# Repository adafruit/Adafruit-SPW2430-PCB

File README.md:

## Adafruit Silicon MEMS Microphone Breakout SPW2430 PCB
<a href="http://www.adafruit.com/products/2716"><br/>
Click here to purchase one from the Adafruit shop</a>

Listen to this good news - we now have a breakout board for a super tiny MEMS microphone. Just like 'classic' electret microphones, MEMS mics can detect sound and convert it to voltage, but they don't need a bias resistor or amplifier, its all in one! The SPW2430 is a small, low cost MEMS mic with a range of 100Hz - 10KHz, good for just about all general audio recording/detection.

This breakout is best used for projects such as voice changers, audio recording/sampling, and audio-reactive projects that use FFT. To keep the breakout small and simple, we only added a 3V voltage regulator (the microphone requires 3.3V DC) and filter capacitors. No additional opamp is included, the output peak-to-peak voltage has a 0.67V DC bias and about 100mVpp (peak-to-peak) when talking near the microphone, which is good for attaching to something that expects 'line level' input without clipping. The peak-to-peak can be as high as 1Vpp if there's a very loud sound. If you are If you need a microphone with adjustable gain or auto-gain control, check out our mic+amplifier options. If you need a higher peak-to-peak, a rail-to-rail op-amp and some resistors can get you boosted up!

Using it is simple: connect GND to ground, Vin to 3.3-5VDC. For the best performance, use the "quietest" supply available (on an Arduino, this would be the 3.3V supply). The audio waveform will come out of the DC pin. The output will have a DC bias of 0.67V so when its perfectly quiet that's what you'll read, there's a little drift. If the audio equipment you're using requires AC coupled audio, you can grab the signal out of the AC pin, which has a 10uF capacitor in series.

This repo contains the PCB files for the Adafruit SPW2430 Breakout

### License

Adafruit invests time and resources providing this open source design, please support Adafruit and open-source hardware by purchasing products from [Adafruit](https://www.adafruit.com)!

All text above must be included in any redistribution

Designed by Limor Fried/Ladyada for Adafruit Industries.
Creative Commons Attribution/Share-Alike, all text above must be included in any redistribution. 
See license.txt for additional information.

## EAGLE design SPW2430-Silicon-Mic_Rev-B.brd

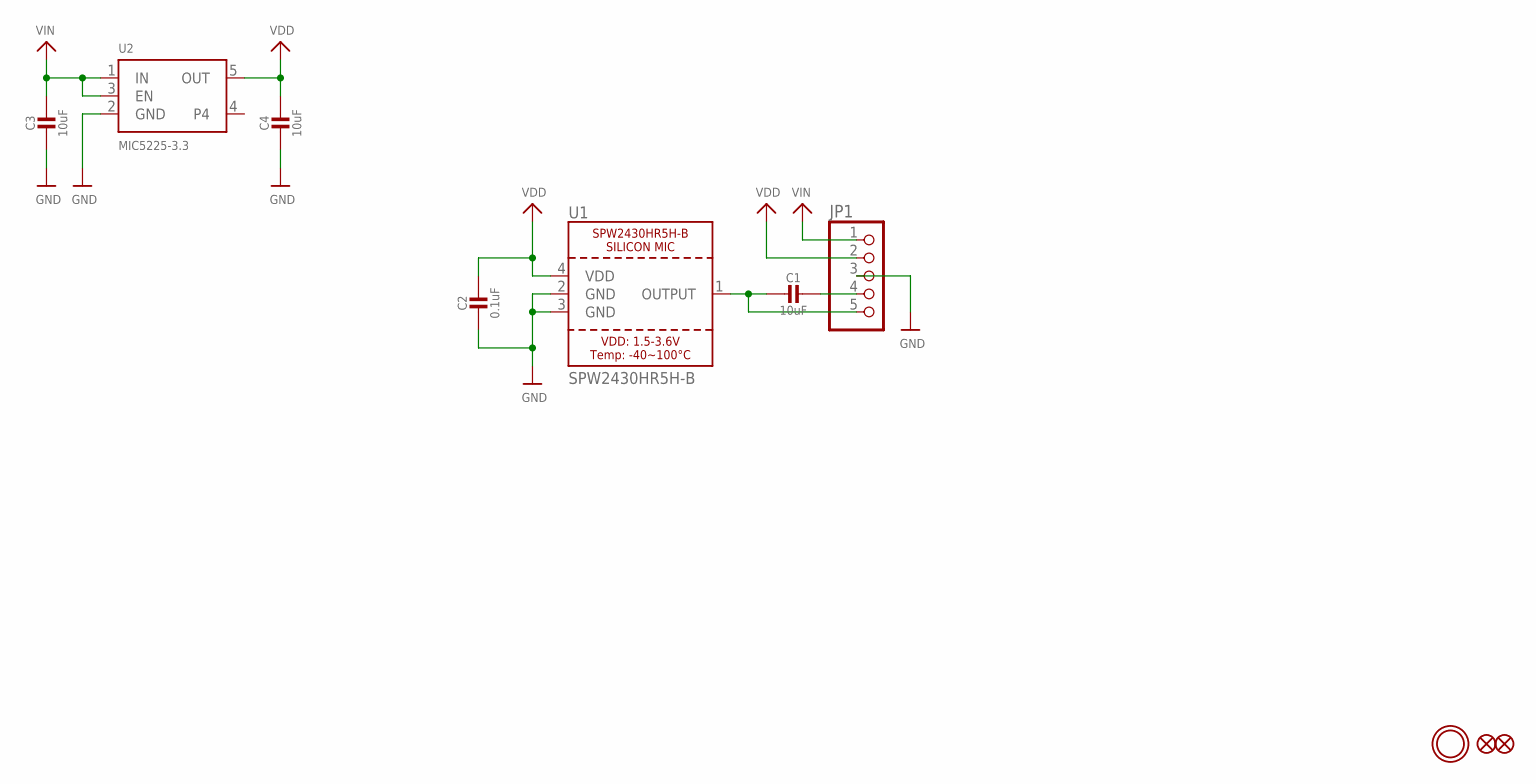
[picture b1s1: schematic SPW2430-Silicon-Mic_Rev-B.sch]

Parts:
C1, C3, C4: 10uF; 0805-NO
C2: 0.1uF; 0805-NO
FID1, FID2: FIDUCIAL""; FIDUCIAL_1MM
JP1: HEADER-1X576MIL; 1X05_ROUND_76
U1: SPW2430HR5H-B
U2: MIC5225-3.3; SOT23-5
U$12: MOUNTINGHOLE2.5; MOUNTINGHOLE_2.5_PLATED

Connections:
GND: C2.2, C3.2, C4.2, JP1.3, U1.2 (GND), U1.3 (GND), U2.2 (GND)
unnamed: C1.2, JP1.5, U1.1 (OUTPUT)
unnamed: C1.1, JP1.4
VDD: C2.1, C4.1, JP1.2, U1.4 (VDD), U2.5 (OUT)
VIN: C3.1, JP1.1, U2.1 (IN), U2.3 (EN)

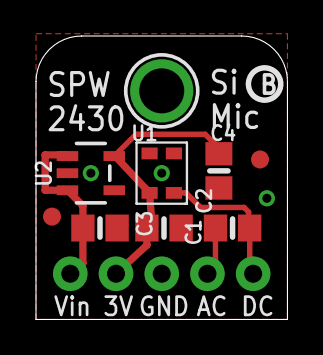
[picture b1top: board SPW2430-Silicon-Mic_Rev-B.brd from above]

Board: 2 copper layers, 14.0 x 15.7 mm, 12 parts (1 on the bottom side), 5 nets.

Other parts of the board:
U$5: ADAFRUIT_3.5MM
U$13: PCBFEAT-REV-040

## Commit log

2016-02-25 init

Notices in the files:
parts and their libraries:
microbuilder: This work is placed in the public domain, and may be freely used for commercial and non-commercial work with the following conditions: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
